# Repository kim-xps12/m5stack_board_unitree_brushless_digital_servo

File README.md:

# Unitree Servo UART Board for M5Stack

## About
M5Stack (AtomS3R など) から Unitree J288 / S288 ブラシレスデジタルサーボを操作するためのオリジナル基板です．KiCad 9 で設計しました．
サーボのバスは 1 本の信号線で送受信する半二重の TTL バス (8N1，4 Mbps) です．この基板は 4 Mbps だけを扱います．サーボのボーレートは，使う前に Unitree の公式ツールで 4 Mbps に変更しておいてください．送信と受信の切り替えは，基板が TX 信号から自動で行います．マイコン側に方向制御用のピンは要りません．ロジックはすべて 3.3 V です．
JLCPCB の部品実装 (PCBA) にそのまま発注できるように作っています．

This board connects Unitree J288 / S288 brushless digital servos to an M5Stack controller (e.g. AtomS3R). The servo bus is a single-wire, half-duplex TTL bus (8N1, 4 Mbps). The board supports 4 Mbps only: change the baud rate of the servos to 4 Mbps with the official Unitree tool before use. The board switches between transmit and receive by itself from the TX signal, so the controller needs no direction pin. All logic runs at 3.3 V. The design is ready for JLCPCB assembly (PCBA).

## Appearance

3D モデルの表示です (実物の写真ではありません)．

## Schematics

## Pin assign

| コネクタ | 部品 | ピン |
| --- | --- | --- |
| J2 (M5Stack と接続) | Grove，HY2.0-4P | Rx = 基板からの受信データ (M5Stack の RX へ)，Tx = M5Stack の TX から，V = 5 V，G = GND |
| J1 (サーボ電源) | XT30UPB-M | + = BAT (F1 を通ってサーボへ)，− = GND |
| F1 (ヒューズ) | ミニ平型ヒューズのホルダー (XFCN XF-508P-B-B) | J1 の + とサーボの BAT の間．ヒューズは付属しません |
| J3〜J7 (サーボ) | JST PH 2.0 3 ピン | 1 = GND，2 = BAT，3 = Signal (サーボ本体のコネクタと同じ番号) |
| TP1 | テストパッド | 送信イネーブル信号 (TXEN) の確認用 |

- J2 の並びは M5Stack の PORT.C (黄 = TX，白 = RX) と同じです．ストレートの Grove ケーブルでつなぎます．AtomS3R では G2 が TX，G1 が RX です．
- J3〜J7 は 5 個とも並列です．サーボ本体のコネクタと同じピン番号なので，サーボに付属の PH 2.0 ケーブル (両端の同じ番号のピン同士がつながるもの) をそのまま挿せます．
- F1 にはミニ平型ヒューズ (自動車用，32 V) を差します．ヒューズは基板に付いていないので，カー用品店などで用意してください．定格は，つなぐサーボの最大電流の合計の 1.33 倍以上を目安に選びます．J288 を 5 台つなぐなら 15 A，1〜2 台なら 5 A です．J1 の XT30 の定格に合わせ，15 A より大きいヒューズは使わないでください．
- F1 は基板と電源配線の短絡から守るためのものです．1 つのポートだけに流れる過電流 (PH は 1 ピン 2 A) は防げません．
- J2 の 5 V で基板のロジック (3.3 V レギュレータ) が動きます．基板から M5Stack へは給電しないので，M5Stack は USB などで別に給電してください．

## Specifications

| 項目 | 値 |
| --- | --- |
| 外形 | 50 × 35 mm (角 R1)，M3 取り付け穴 × 4 (40 × 25 mm 間隔) |
| サーボ電源 | J1 から入力．Unitree の推奨値は J288 が 25.2 V，S288 が 12.6 V (最低 6.4 V) |
| ヒューズ | ミニ平型 (Littelfuse MINI 297 / Bussmann ATM 相当，32 V)．J288 × 5 台で 15 A．付属しない |
| 入力コンデンサ | 100 µF 50 V (C7，F1 の後ろ) |
| ポートの電流 | 1 ピン 2 A (JST PH)．全力運転の J288 (最大 1.92 A) は 1 ポートに 1 台まで |
| 通信 | 半二重 TTL，3.3 V，4 Mbps (8N1) のみ．サーボは使う前に公式ツールで 4 Mbps に設定する |

## Layout

## BOM

| 記号 | 部品 | 値 | LCSC |
| --- | --- | --- | --- |
| U1 | 74LVC1G14 (SOT-23-5) | シュミットトリガ・インバータ | C7835 |
| U2 | XC6206P332MR (SOT-23) | 3.3 V レギュレータ | C5446 |
| U3 | 74LVC1G126 (SOT-23-5) | バスドライバ | C7834 |
| U4 | 74LVC1G125 (SOT-23-5) | 受信バッファ | C23654 |
| D1 | RB751V-40 (SOD-323) | ショットキーダイオード | C7502691 |
| R1，R2，R3，R4 | 0603 | 68k，47，10k，470 | C23231，C23182，C25804，C23179 |
| C1，C4，C5 | 0603 | 0.1 µF | C14663 |
| C2，C3 | 0603 | 1 µF | C15849 |
| C6 | 0603，C0G | 100 pF | C14858 |
| C7 | 電解コンデンサ 6.3 × 7.7 mm | 100 µF 50 V | C3445238 |
| J1 | XT30UPB-M | | C428721 |
| F1 | XFCN XF-508P-B-B (ミニ平型ヒューズのホルダー，絶縁ブロック付き) | ヒューズは付属しない | C19727305 |
| J2 | ZX-HY2.0-4PZZ | | C7429580 |
| J3〜J7 | JST B3B-PH-K-S(LF)(SN) | | C131339 |

## Example code

サンプルコードは準備中です．AtomS3R では UART を TX = G2，RX = G1 に割り当て，4 Mbps (4,000,000 bps) で通信します．

## JLCPCB で製造する

`tools/jlcpcb_export.py` を KiCad 同梱の Python で実行すると，JLCPCB の部品実装 (PCBA) に使うファイルが `production/` (git 管理外) に出力されます．

```bash
/Applications/KiCad/KiCad.app/Contents/Frameworks/Python.framework/Versions/Current/bin/python3 tools/jlcpcb_export.py
```

- `gerber_jlcpcb.zip`: ガーバーとドリル
- `bom_jlcpcb.csv`: BOM
- `cpl_jlcpcb.csv`: 部品の配置 (JLCPCB のランドパターンに合わせて回転と原点を補正済み)

部品本体はすべて基板端から 2.5 mm 以上離してあるので，Economic PCBA でエッジレールなしで発注できます．
JLCPCB の製造能力 (2 層，1 oz) の推奨値は DRC のルールファイル `m5stack_board_unitree_brushless_digital_servo.kicad_dru` に入れてあり，KiCad の DRC でそのまま確認できます．
F1 は BOM ではホルダーとして出力します (コメント「XF-508P-B-B fuse holder (fuse not included)」)．ヒューズ本体は JLCPCB では実装しません．
KiCad のプラグインや，基板ファイルをそのまま JLCPCB にアップロードする方法は使わないでください．部品ごとの回転と原点の補正が入らず，C7 の極性や J3〜J7 の向きが逆になります．
発注時は，JLCPCB の配置プレビューで部品の向き (D1，IC の 1 番ピン，C7 の極性，コネクタ) を確認してください．
J3〜J7 はプレビューで箱として表示されます．箱の左下に 1 番ピンの目印「[」が見え，箱の右にシルクの枠がはみ出していなければ，正しい向きです (逆向きだと箱が 1.1 mm 左にずれます)．

To make the files for JLCPCB assembly (Gerber, BOM, CPL), run `tools/jlcpcb_export.py` with the Python bundled with KiCad (command above). The files are written to `production/`. Every component body is at least 2.5 mm from the board edge, so Economic PCBA works without edge rails. The DRC rule file holds JLCPCB's recommended values (2 layers, 1 oz). The BOM lists F1 as the fuse holder only; the fuse itself is not assembled. Do not use KiCad plugins or a direct upload of the board file: they miss the per-part rotation and origin corrections (C7 polarity, J3-J7 orientation). Check the placement preview when ordering. J3-J7 show as plain boxes there: they face the right way when the pin-1 mark "[" shows at the lower left of each box and no silkscreen outline sticks out on its right (a reversed connector shifts its box 1.1 mm to the left).

## NOTE
J1 (XT30UPB)，J2 (HY2.0-4P)，F1 (ミニ平型ヒューズのホルダー XFCN XF-508P-B-B) のフットプリントは，プロジェクト内のライブラリ `Library.pretty` (`fp-lib-table` に登録済み) にあります．
ほかの部品も，KiCad 標準ライブラリのフットプリントをシルクの線幅だけ 0.15 mm に太らせたコピーを `Library.pretty` に置いて使っています (JLCPCB では 0.15 mm 未満の線や文字が判読できないため)．PH コネクタはパッド幅も 1.25 mm に広げています (JLCPCB 推奨のランド幅 0.25 mm)．
J1，J2，F1 の 3D モデル (STEP) はリポジトリに含めていません．3D ビューアや STEP 出力で表示するには，リポジトリのルートで次のコマンドを実行してください．LCSC の部品 C428721 (J1)，C7429580 (J2)，C19727305 (F1) の 3D モデルを EasyEDA から取得し，`Library.3dshapes/` に保存します (easyeda2kicad 1.0.1 で確認)．

```bash
pip install easyeda2kicad
easyeda2kicad --3d --lcsc_id C428721 C7429580 C19727305 --output Library
```

The footprints of J1 (XT30UPB), J2 (HY2.0-4P) and F1 (MINI blade fuse holder XFCN XF-508P-B-B) are in the project library `Library.pretty` (registered in `fp-lib-table`).
The other parts also use copies of the KiCad library footprints in `Library.pretty`, changed only in the silkscreen width (0.15 mm), because JLCPCB cannot print legible lines or characters thinner than 0.15 mm. The PH connector copy also has 1.25 mm wide pads (JLCPCB's recommended 0.25 mm annular ring).
The 3D models (STEP) of J1, J2 and F1 are not included in this repository. To show them in the 3D viewer or in a STEP export, run the commands above in the repository root. They download the 3D models of LCSC parts C428721 (J1), C7429580 (J2) and C19727305 (F1) from EasyEDA into `Library.3dshapes/` (checked with easyeda2kicad 1.0.1).

## Disclaimer
MITライセンスでの公開です．本設計において生じた一切の損害等について作者は責任を負いません．予めご了承ください．

This is released under the MIT license. The author is not responsible for any damage caused by this design. Please note.

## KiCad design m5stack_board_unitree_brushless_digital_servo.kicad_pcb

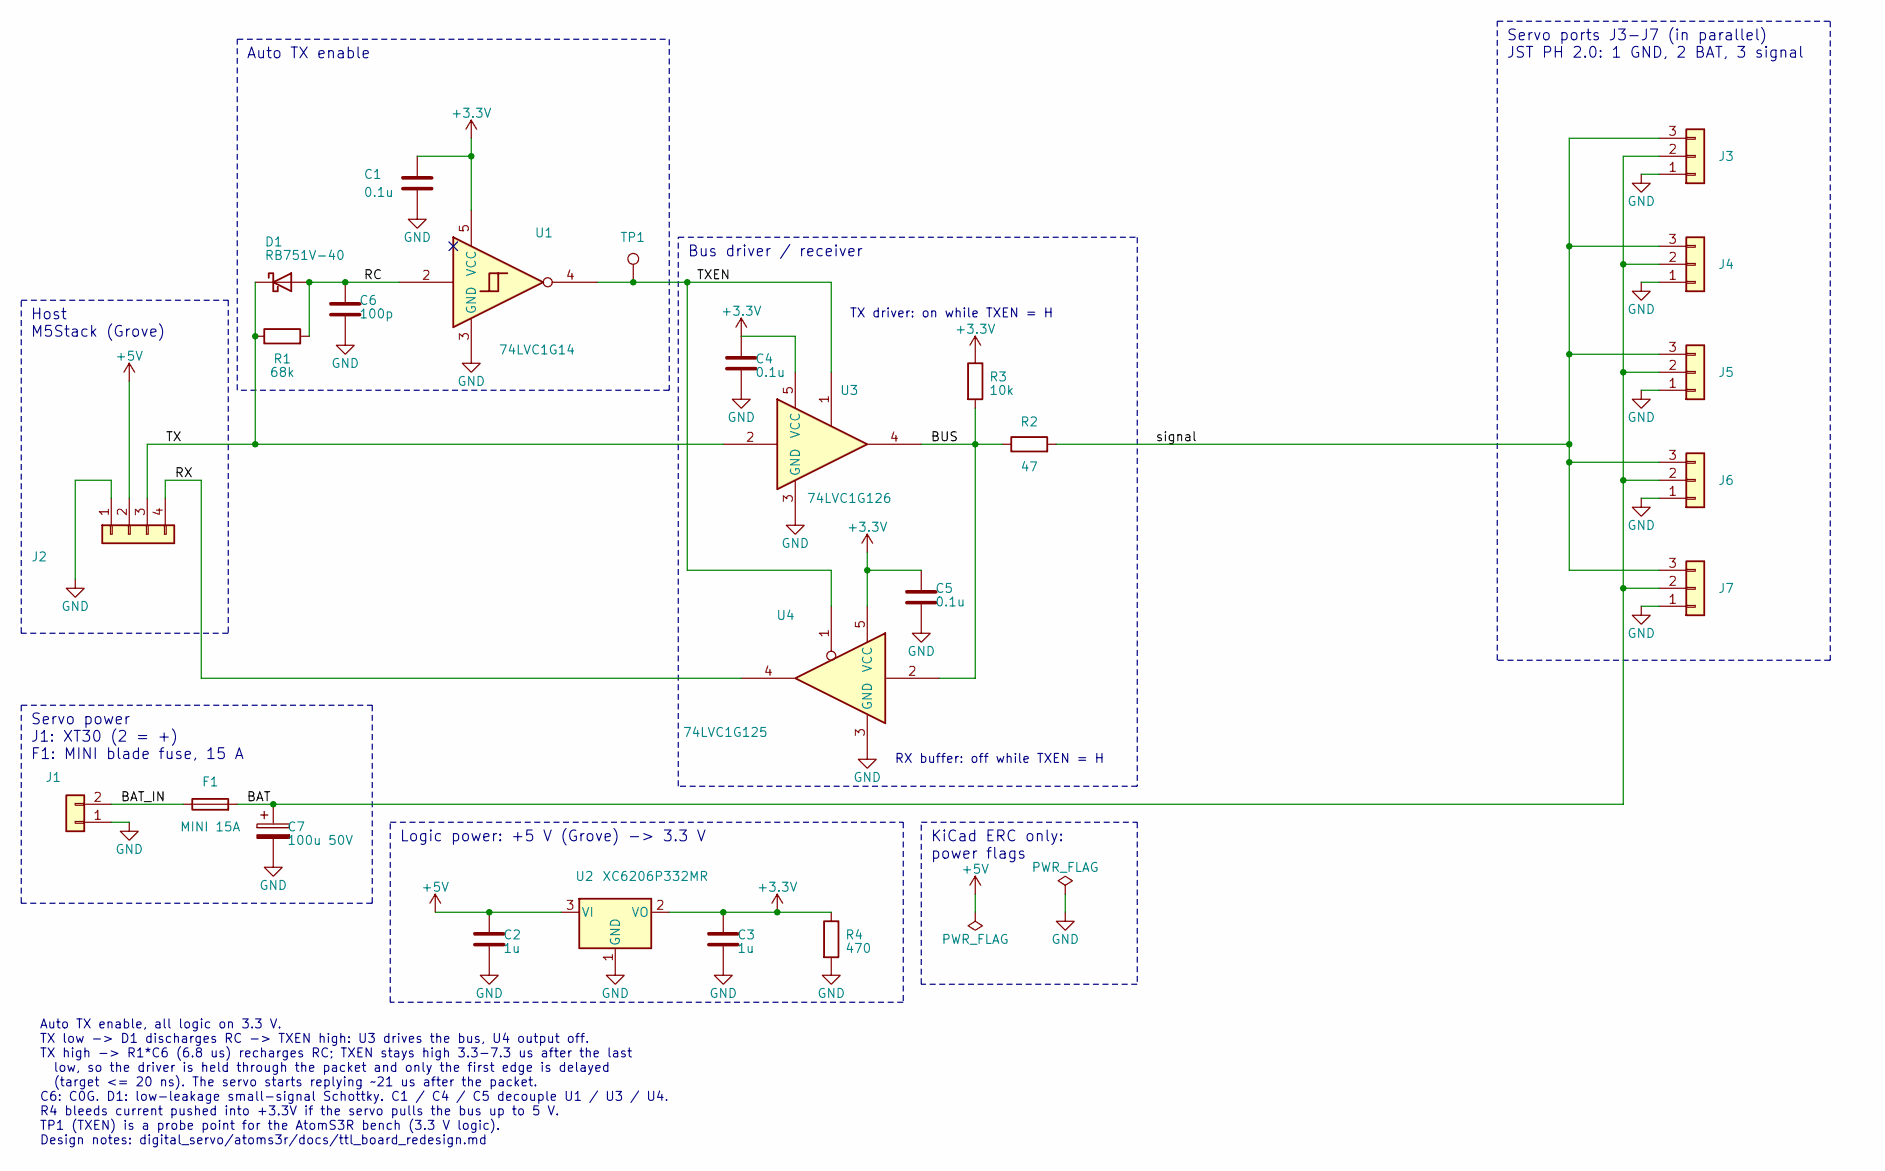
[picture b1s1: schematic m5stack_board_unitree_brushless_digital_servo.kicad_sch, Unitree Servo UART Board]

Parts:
C1, C4, C5: 0.1u; C_0603_1608Metric_Pad1.08x0.95mm_HandSolder; LCSC C14663
C2, C3: 1u; C_0603_1608Metric_Pad1.08x0.95mm_HandSolder; LCSC C15849
C6: 100p; C_0603_1608Metric_Pad1.08x0.95mm_HandSolder; LCSC C14858
C7: 100u 50V; CP_Elec_6.3x7.7; LCSC C3445238
D1: RB751V-40; D_SOD-323_HandSoldering; LCSC C7502691
F1: MINI 15A; Fuseholder_Blade_Mini_XFCN_XF-508P-B-B; LCSC C19727305
J1: XT30UPB-M; AMASS_XT30UPB-M_1x02_P5.0mm_Vertical; LCSC C428721
J2: ZX-HY2.0-4PZZ; HY2.0-4P_1x04_P2.00mm_Vertical; LCSC C7429580
J3, J4, J5, J6, J7: B3B-PH-K-S(LF)(SN); JST_PH_B3B-PH-K_1x03_P2.00mm_Vertical; LCSC C131339
R1: 68k; R_0603_1608Metric_Pad0.98x0.95mm_HandSolder; LCSC C23231
R2: 47; R_0603_1608Metric_Pad0.98x0.95mm_HandSolder; LCSC C23182
R3: 10k; R_0603_1608Metric_Pad0.98x0.95mm_HandSolder; LCSC C25804
R4: 470; R_0603_1608Metric_Pad0.98x0.95mm_HandSolder; LCSC C23179
TP1: TXEN; TestPoint_THTPad_D1.5mm_Drill0.7mm
U1: 74LVC1G14; SOT-23-5_HandSoldering; LCSC C7835
U2: XC6206P332MR; SOT-23; LCSC C5446
U3: 74LVC1G126; SOT-23-5_HandSoldering; LCSC C7834
U4: 74LVC1G125; SOT-23-5_HandSoldering; LCSC C23654

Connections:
+3.3V: C1.1, C3.1, C4.1, C5.1, R3.1, R4.1, U1.5 (VCC), U2.2 (VO), U3.5 (VCC), U4.5 (VCC)
+5V: C2.1, J2.2, U2.3 (VI)
/BAT: C7.1, F1.2, J3.2, J4.2, J5.2, J6.2, J7.2
/BAT_IN: F1.1, J1.2
/BUS: R2.1, R3.2, U3.4, U4.2
/RC: C6.1, D1.2 (A), R1.2, U1.2
/RX: J2.4, U4.4
/TX: D1.1 (K), J2.3, R1.1, U3.2
/TXEN: TP1.1, U1.4, U3.1, U4.1
/signal: J3.3, J4.3, J5.3, J6.3, J7.3, R2.2
GND: C1.2, C2.2, C3.2, C4.2, C5.2, C6.2, C7.2, J1.1, J2.1, J3.1, J4.1, J5.1, J6.1, J7.1, R4.2, U1.3 (GND), U2.1 (GND), U3.3 (GND), U4.3 (GND)

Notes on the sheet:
Host M5Stack (Grove)
Auto TX enable
TX driver: on while TXEN = H
Bus driver / receiver
RX buffer: off while TXEN = H
Servo ports J3-J7 (in parallel) JST PH 2.0: 1 GND, 2 BAT, 3 signal
Servo power J1: XT30 (2 = +) F1: MINI blade fuse, 15 A
Logic power: +5 V (Grove) -> 3.3 V
KiCad ERC only: power flags
Auto TX enable, all logic on 3.3 V. TX low -> D1 discharges RC -> TXEN high: U3 drives the bus, U4 output off. TX high -> R1*C6 (6.8 us) recharges RC; TXEN stays high 3.3-7.3 us after the last low, so the driver is held through the packet and only the first edge is delayed (target <= 20 ns). The se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

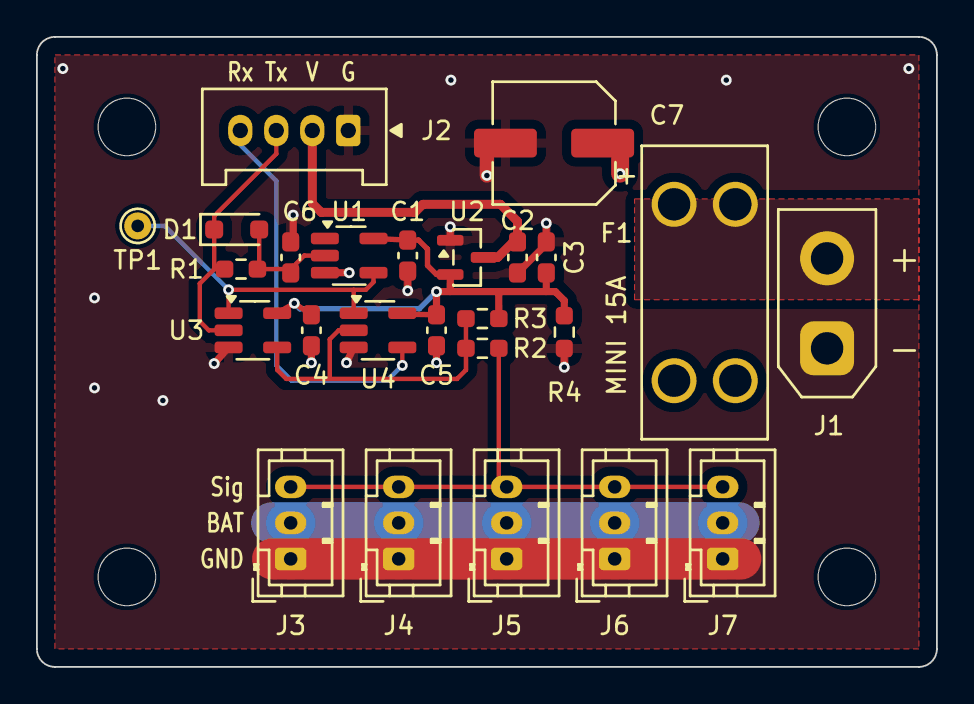
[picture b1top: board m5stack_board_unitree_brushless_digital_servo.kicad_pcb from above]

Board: 2 copper layers, 50.0 x 35.0 mm, 29 parts (0 on the bottom side), 11 nets.

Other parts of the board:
MH1, MH2, MH3, MH4: MountingHole_3.2mm_M3
